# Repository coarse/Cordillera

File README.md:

# Cordillera

## About

The Cordillera PCB is an open design PCB heavily based on the Alice PCB. The only breaking change is the USB connector which renders it unusable on most Alice cases.

- STM32F072 controller
- USB C connector mounted at the top
- ESD, over voltage, and over current protection circuits
- Dual common cathode diodes instead of single ones
- Backlight, single color
- Fancy "press to reset, hold for bootloader" reset circuit

## Dependencies

Symbols and footprints used are from my [KiCad library](https://github.com/coarse/KiCad-Keeb-Lib)

## Notes

- Original Alice uses USB Mini, so this PCB may be incompatible with some Alice cases

## Disclaimer

I provide this design as a reference for designing similar keyboard layout PCBs. Using them within your projects will require a will to do research of one's own and to learn the workings of them, potentially fixing issues if they exist.

I present the design as-is and as-available, without liability and without any guarantees regarding functionality, as expressed in the license.

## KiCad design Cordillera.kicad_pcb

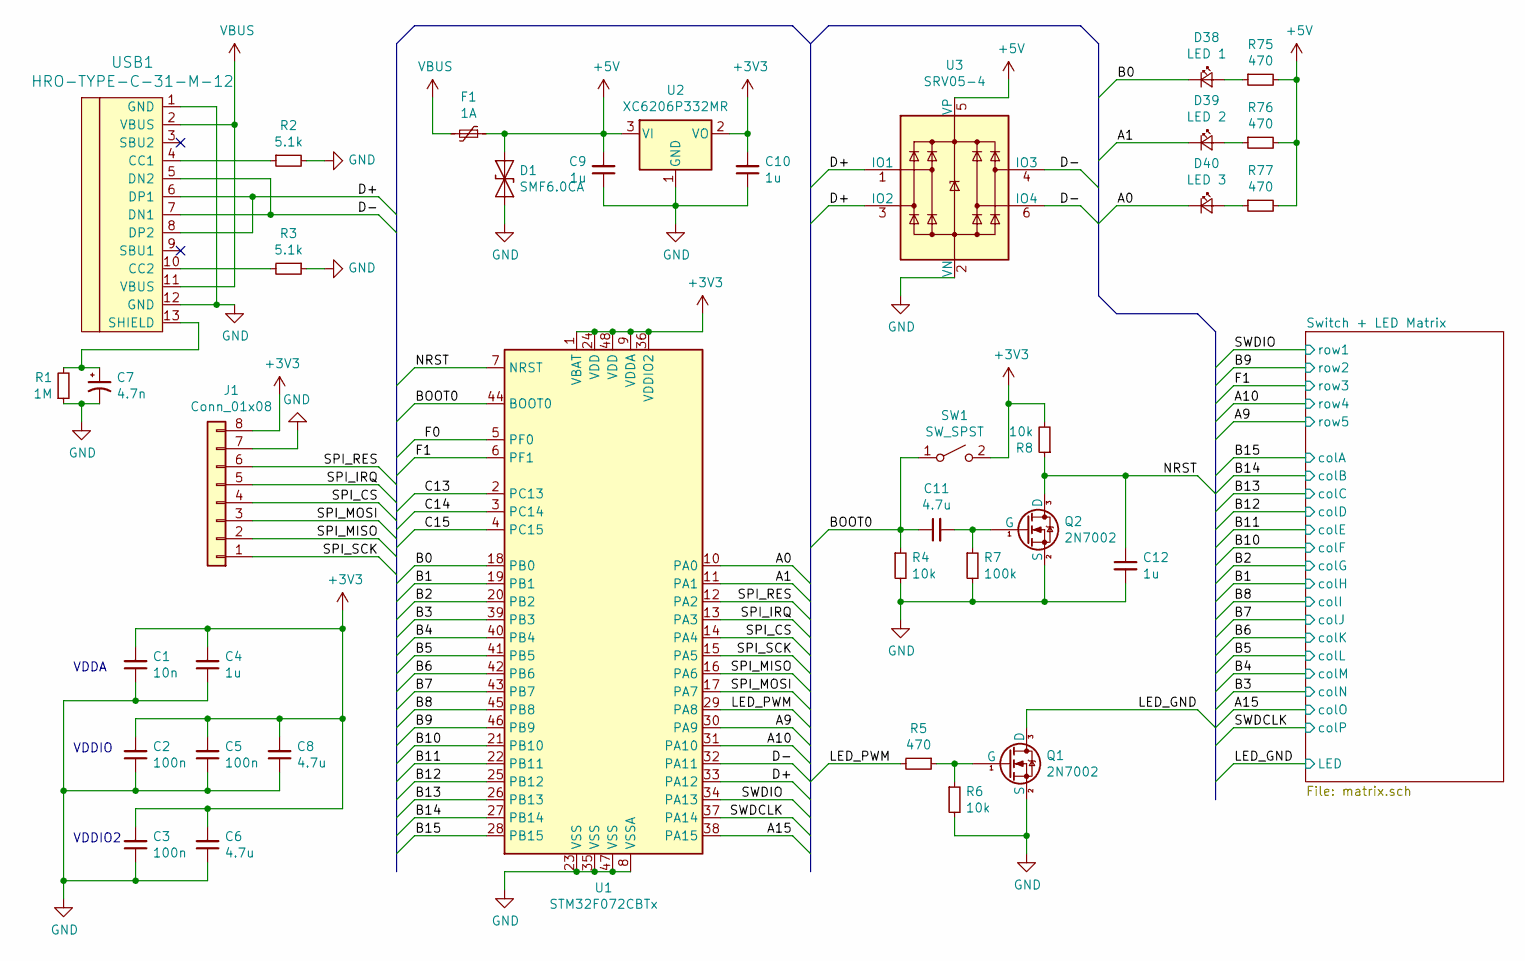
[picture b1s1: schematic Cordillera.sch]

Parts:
C1: 10n; C_0603_1608Metric
C2, C3, C5: 100n; C_0603_1608Metric
C4, C9, C10, C12: 1u; C_0603_1608Metric
C6, C8, C11: 4.7u; C_0603_1608Metric
C7: 4.7n; C_0603_1608Metric
D1: SMF6.0CA; D_SOD-123
D38: LED 1; LED_D3.0mm
D39: LED 2; LED_D3.0mm
D40: LED 3; LED_D3.0mm
F1: 1A; Fuse_1206_3216Metric
J1: Conn_01x08; PinHeader_2x04_P2.54mm_Vertical
Q1, Q2: 2N7002; SOT-23
R1: 1M; R_0603_1608Metric
R2, R3: 5.1k; R_0603_1608Metric
R4, R6, R8: 10k; R_0603_1608Metric
R5, R75, R76, R77: 470; R_0603_1608Metric
R7: 100k; R_0603_1608Metric
SW1: SW_SPST; TactSwitch_SPST_5.1x5.1mm
U1: STM32F072CBTx; LQFP-48_7x7mm_P0.5mm
U2: XC6206P332MR; SOT-23
U3: SRV05-4; SOT-23-6
USB1: HRO-TYPE-C-31-M-12

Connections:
+3V3: C1.2, C2.2, C3.2, C4.2, C5.2, C6.2, C8.2, C10.2, J1.8, R8.2, SW1.2 (B), U1.1 (VBAT), U1.9 (VDDA), U1.24 (VDD), U1.36 (VDDIO2), U1.48 (VDD), U2.2 (VO)
+5V: C9.2, D1.1 (A1), F1.1, R75.2, R76.2, R77.2, U2.3 (VI), U3.5 (VP); also elsewhere on the board
/A0: D40.1 (K), U1.10 (PA0)
/A1: D39.1 (K), U1.11 (PA1)
/A9: U1.30 (PA9); also elsewhere on the board
/A10: U1.31 (PA10); also elsewhere on the board
/A15: U1.38 (PA15); also elsewhere on the board
/B0: D38.1 (K), U1.18 (PB0)
/B1: U1.19 (PB1); also elsewhere on the board
/B2: U1.20 (PB2); also elsewhere on the board
/B3: U1.39 (PB3); also elsewhere on the board
/B4: U1.40 (PB4); also elsewhere on the board
/B5: U1.41 (PB5); also elsewhere on the board
/B6: U1.42 (PB6); also elsewhere on the board
/B7: U1.43 (PB7); also elsewhere on the board
/B8: U1.45 (PB8); also elsewhere on the board
/B9: U1.46 (PB9); also elsewhere on the board
/B10: U1.21 (PB10); also elsewhere on the board
/B11: U1.22 (PB11); also elsewhere on the board
/B12: U1.25 (PB12); also elsewhere on the board
/B13: U1.26 (PB13); also elsewhere on the board
/B14: U1.27 (PB14); also elsewhere on the board
/B15: U1.28 (PB15); also elsewhere on the board
/BOOT0: C11.1, R4.1, SW1.1 (A), U1.44 (BOOT0)
/C13: U1.2 (PC13)
/C14: U1.3 (PC14)
/C15: U1.4 (PC15)
/D+: U1.33 (PA12), U3.1 (IO1), U3.3 (IO2), USB1.6 (DP1), USB1.8 (DP2)
/D-: U1.32 (PA11), U3.4 (IO3), U3.6 (IO4), USB1.5 (DN2), USB1.7 (DN1)
/F0: U1.5 (PF0)
/F1: U1.6 (PF1); also elsewhere on the board
/LED_GND: Q1.3 (D); also elsewhere on the board
/LED_PWM: R5.2, U1.29 (PA8)
/NRST: C12.1, Q2.3 (D), R8.1, U1.7 (NRST)
/SPI_CS: J1.4, U1.14 (PA4)
/SPI_IRQ: J1.5, U1.13 (PA3)
/SPI_MISO: J1.2, U1.16 (PA6)
/SPI_MOSI: J1.3, U1.17 (PA7)
/SPI_RES: J1.6, U1.12 (PA2)
/SPI_SCK: J1.1, U1.15 (PA5)
/SWDCLK: U1.37 (PA14); also elsewhere on the board
/SWDIO: U1.34 (PA13); also elsewhere on the board
GND: C1.1, C2.1, C3.1, C4.1, C5.1, C6.1, C7.2, C8.1, C9.1, C10.1, C12.2, D1.2 (A2), J1.7, Q1.2 (S), Q2.2 (S), R1.1, R2.2, R3.1, R4.2, R6.2, R7.2, U1.8 (VSSA), U1.23 (VSS), U1.35 (VSS), U1.47 (VSS), U2.1 (GND), U3.2 (VN), USB1.1 (GND), USB1.12 (GND)
unnamed: C7.1, R1.2, USB1.13 (SHIELD)
unnamed: C11.2, Q2.1 (G), R7.1
unnamed: D38.2 (A), R75.1
unnamed: D39.2 (A), R76.1
unnamed: D40.2 (A), R77.1
unnamed: Q1.1 (G), R5.1, R6.1
unnamed: R2.1, USB1.4 (CC1)
unnamed: R3.2, USB1.10 (CC2)
VBUS: F1.2, USB1.2 (VBUS), USB1.11 (VBUS)

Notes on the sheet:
VDDIO
VDDIO2
VDDA

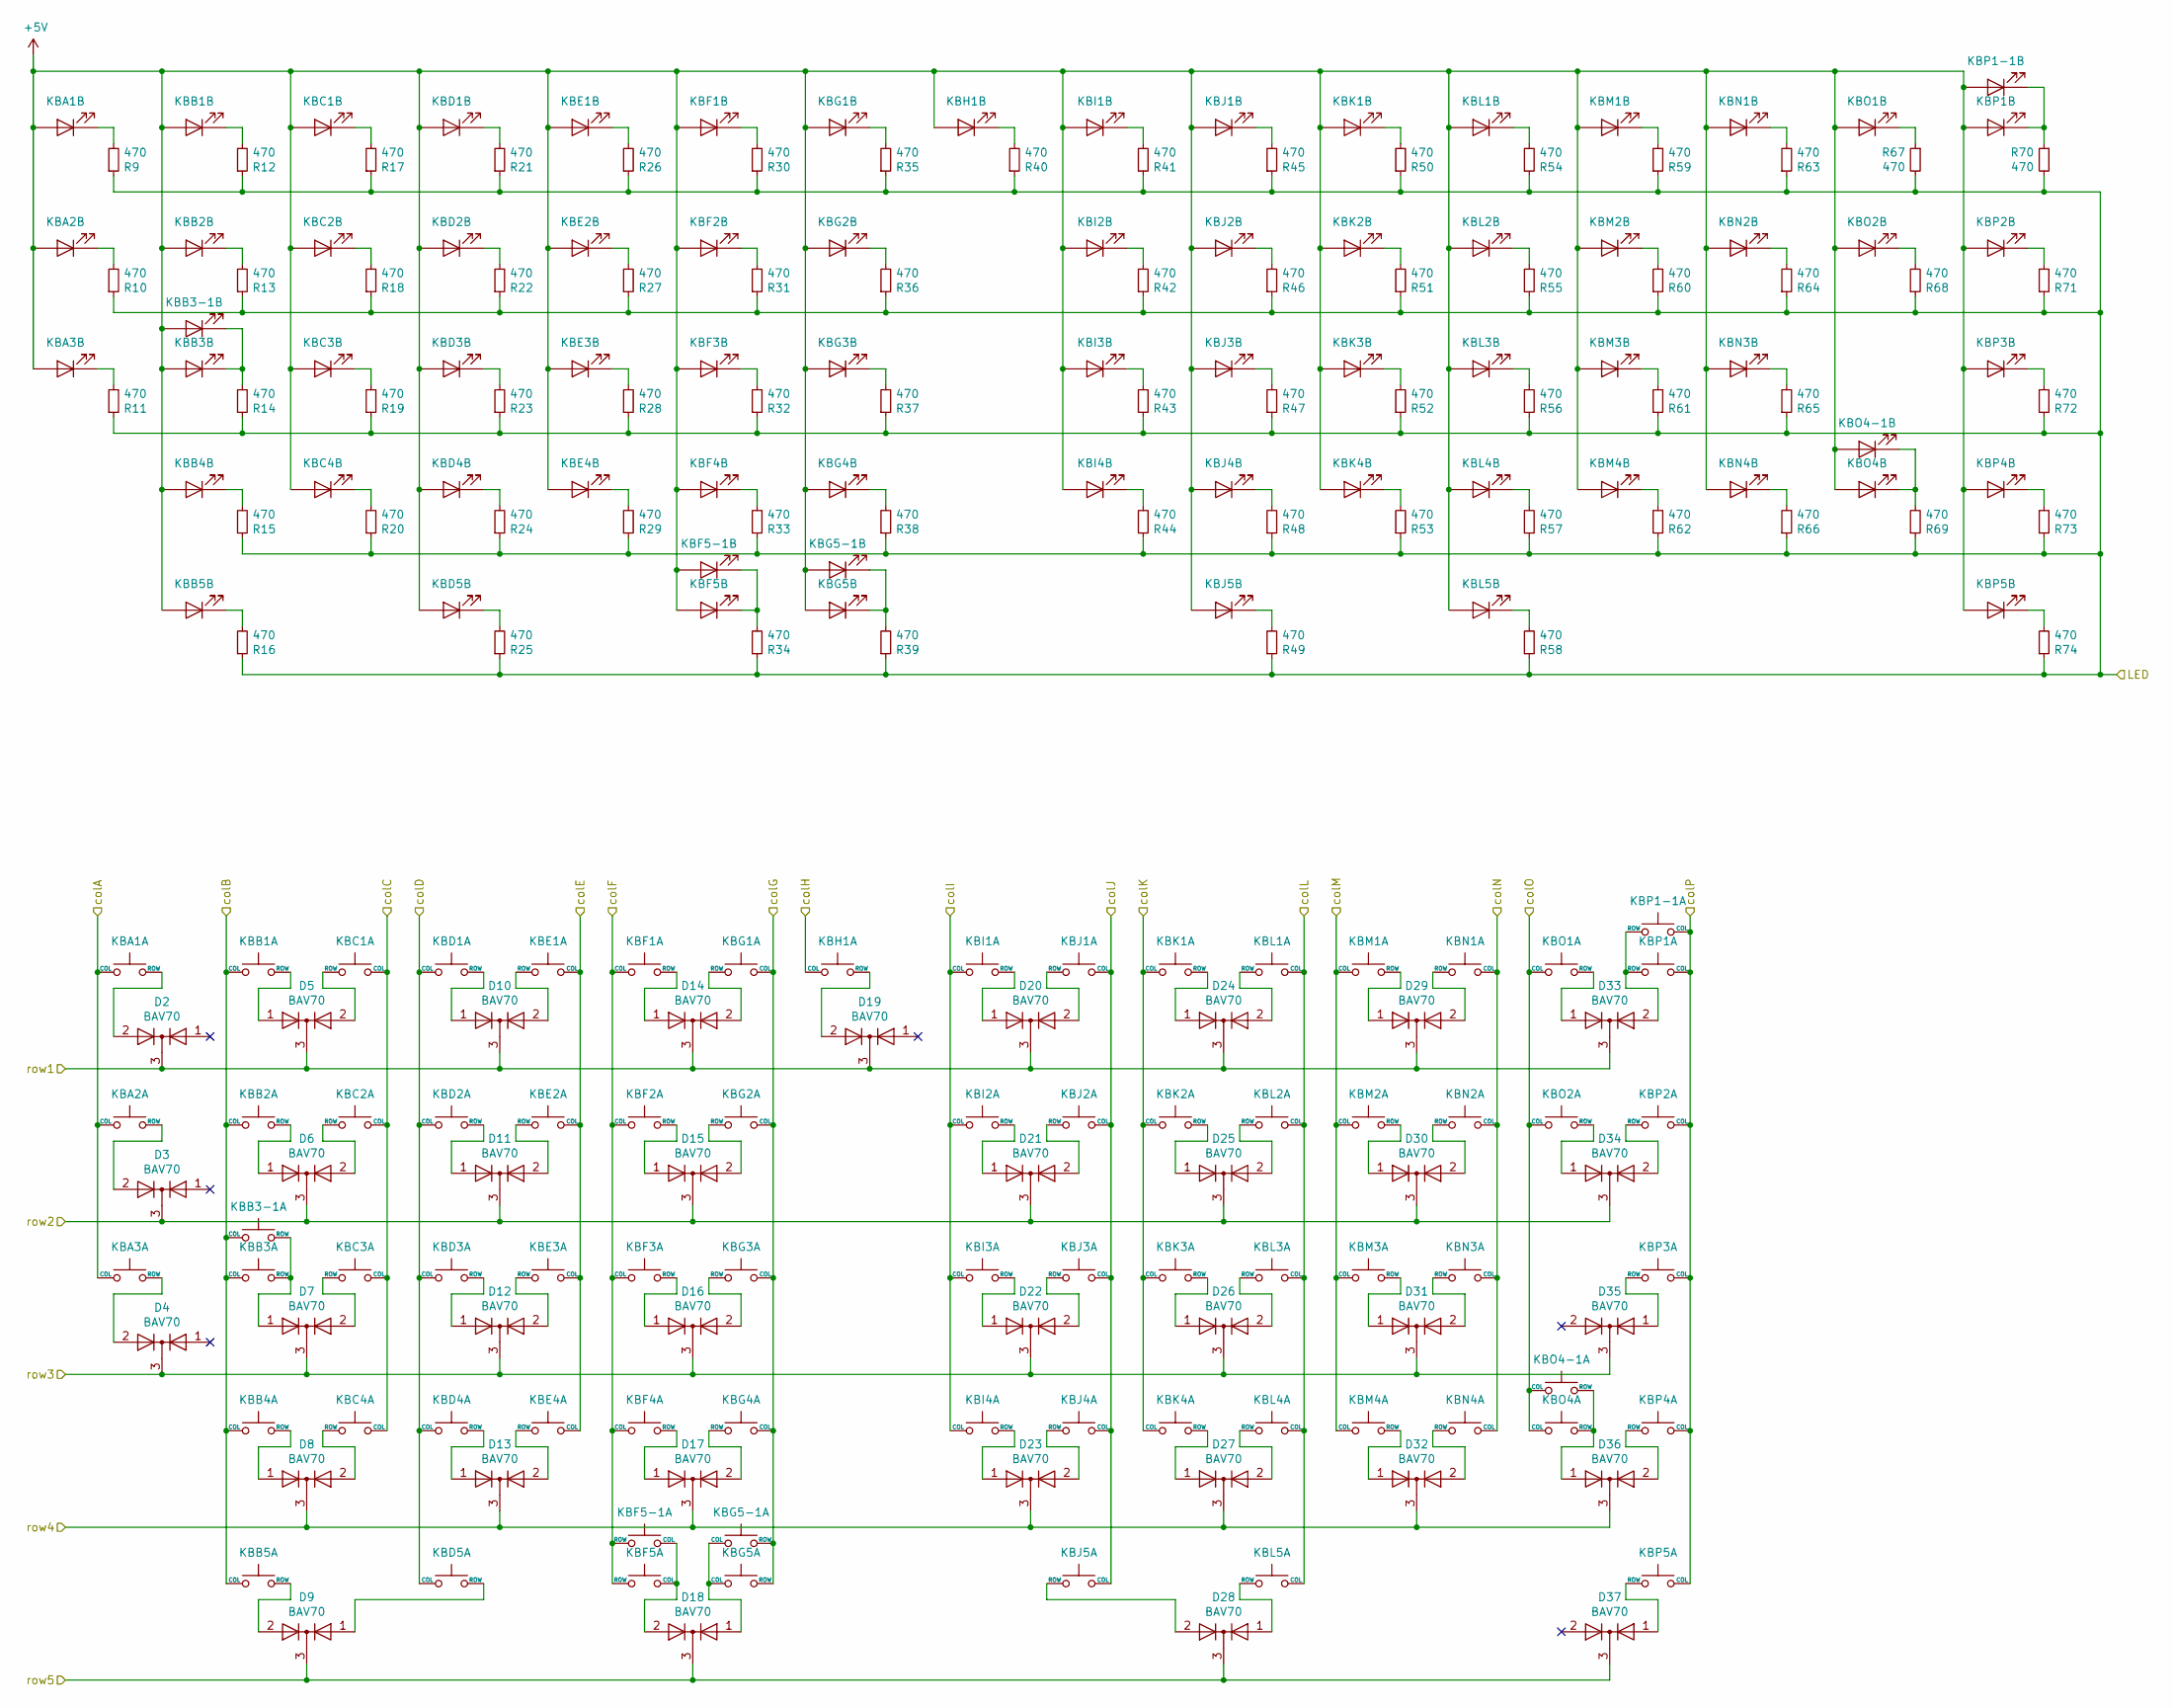
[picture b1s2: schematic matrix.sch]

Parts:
D2, D3, D4, D5, D6, D7, D8, D9, D10, D11, D12, D13, D14, D15, D16, D17, D18, D19, D20, D21, D22, D23, D24, D25, D26, D27, D28, D29, D30, D31, D32, D33, D34, D35, D36, D37: BAV70; SOT-23
KBA1, KBA2, KBA3: Keyboard_Switch; MXOnly-1U
KBB1: Keyboard_Switch; MXOnly-1U
KBB2, KBB5: Keyboard_Switch; MXOnly-1.5U
KBB3: Keyboard_Switch; MXOnly-1.75U
KBB3-1: Keyboard_Switch; MXOnly-1.25U-FLIPPED
KBB4: Keyboard_Switch; MXOnly-2.25U
KBC1, KBC2, KBC3, KBC4: Keyboard_Switch; MXOnly-1U
KBD1, KBD2, KBD3, KBD4: Keyboard_Switch; MXOnly-1U
KBD5: Keyboard_Switch; MXOnly-1.5U
KBE1, KBE2, KBE3, KBE4: Keyboard_Switch; MXOnly-1U
KBF1, KBF2, KBF3, KBF4: Keyboard_Switch; MXOnly-1U
KBF5: Keyboard_Switch; MXOnly-2U-FLIPPED-ReversedStabilizers
KBF5-1: Keyboard_Switch; MXOnly-2.25U-ReversedStabilizers
KBG1, KBG2, KBG3, KBG4, KBG5-1: Keyboard_Switch; MXOnly-1U
KBG5: Keyboard_Switch; MXOnly-1.25U-FLIPPED
KBH1: Keyboard_Switch; MXOnly-1U
KBI1, KBI2, KBI3, KBI4: Keyboard_Switch; MXOnly-1U
KBJ1, KBJ2, KBJ3, KBJ4: Keyboard_Switch; MXOnly-1U
KBJ5: Keyboard_Switch; MXOnly-2.75U-ReversedStabilizers
KBK1, KBK2, KBK3, KBK4: Keyboard_Switch; MXOnly-1U
KBL1, KBL2, KBL3, KBL4: Keyboard_Switch; MXOnly-1U
KBL5: Keyboard_Switch; MXOnly-1.5U
KBM1, KBM2, KBM3, KBM4: Keyboard_Switch; MXOnly-1U
KBN1, KBN2, KBN3, KBN4: Keyboard_Switch; MXOnly-1U
KBO1, KBO2: Keyboard_Switch; MXOnly-1U
KBO4: Keyboard_Switch; MXOnly-2.75U
KBO4-1: Keyboard_Switch; MXOnly-1.75U-FLIPPED
KBP1: Keyboard_Switch; MXOnly-2U
KBP1-1: Keyboard_Switch; MXOnly-1U-FLIPPED
KBP2, KBP5: Keyboard_Switch; MXOnly-1.5U
KBP3: Keyboard_Switch; MXOnly-2.25U-ReversedStabilizers
KBP4: Keyboard_Switch; MXOnly-1U
R9, R10, R11, R12, R13, R14, R15, R16, R17, R18, R19, R20, R21, R22, R23, R24, R25, R26, R27, R28, R29, R30, R31, R32, R33, R34, R35, R36, R37, R38, R39, R40, R41, R42, R43, R44, R45, R46, R47, R48, R49, R50, R51, R52, R53, R54, R55, R56, R57, R58, R59, R60, R61, R62, R63, R64, R65, R66, R67, R68, R69, R70, R71, R72, R73, R74: 470; R_0603_1608Metric

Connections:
+5V: KBA1.3 (LED), KBA2.3 (LED), KBA3.3 (LED), KBB1.3 (LED), KBB2.3 (LED), KBB3.3 (LED), KBB3-1.3 (LED), KBB4.3 (LED), KBB5.3 (LED), KBC1.3 (LED), KBC2.3 (LED), KBC3.3 (LED), KBC4.3 (LED), KBD1.3 (LED), KBD2.3 (LED), KBD3.3 (LED), KBD4.3 (LED), KBD5.3 (LED), KBE1.3 (LED), KBE2.3 (LED), KBE3.3 (LED), KBE4.3 (LED), KBF1.3 (LED), KBF2.3 (LED), KBF3.3 (LED), KBF4.3 (LED), KBF5.3 (LED), KBF5-1.3 (LED), KBG1.3 (LED), KBG2.3 (LED), KBG3.3 (LED), KBG4.3 (LED), KBG5.3 (LED), KBG5-1.3 (LED), KBH1.3 (LED), KBI1.3 (LED), KBI2.3 (LED), KBI3.3 (LED), KBI4.3 (LED), KBJ1.3 (LED), KBJ2.3 (LED), KBJ3.3 (LED), KBJ4.3 (LED), KBJ5.3 (LED), KBK1.3 (LED), KBK2.3 (LED), KBK3.3 (LED), KBK4.3 (LED), KBL1.3 (LED), KBL2.3 (LED), KBL3.3 (LED), KBL4.3 (LED), KBL5.3 (LED), KBM1.3 (LED), KBM2.3 (LED), KBM3.3 (LED), KBM4.3 (LED), KBN1.3 (LED), KBN2.3 (LED), KBN3.3 (LED), KBN4.3 (LED), KBO1.3 (LED), KBO2.3 (LED), KBO4.3 (LED), KBO4-1.3 (LED), KBP1.3 (LED), KBP1-1.3 (LED), KBP2.3 (LED), KBP3.3 (LED), KBP4.3 (LED), KBP5.3 (LED); also elsewhere on the board
/A9: D9.3 (K), D18.3 (K), D28.3 (K), D37.3 (K); also elsewhere on the board
/A10: D8.3 (K), D13.3 (K), D17.3 (K), D23.3 (K), D27.3 (K), D32.3 (K), D36.3 (K); also elsewhere on the board
/A15: KBO1.1 (COL), KBO2.1 (COL), KBO4.1 (COL), KBO4-1.1 (COL); also elsewhere on the board
/B1: KBH1.1 (COL); also elsewhere on the board
/B2: KBG1.1 (COL), KBG2.1 (COL), KBG3.1 (COL), KBG4.1 (COL), KBG5.2 (ROW), KBG5-1.2 (ROW); also elsewhere on the board
/B3: KBN1.1 (COL), KBN2.1 (COL), KBN3.1 (COL), KBN4.1 (COL); also elsewhere on the board
/B4: KBM1.1 (COL), KBM2.1 (COL), KBM3.1 (COL), KBM4.1 (COL); also elsewhere on the board
/B5: KBL1.1 (COL), KBL2.1 (COL), KBL3.1 (COL), KBL4.1 (COL), KBL5.1 (COL); also elsewhere on the board
/B6: KBK1.1 (COL), KBK2.1 (COL), KBK3.1 (COL), KBK4.1 (COL); also elsewhere on the board
/B7: KBJ1.1 (COL), KBJ2.1 (COL), KBJ3.1 (COL), KBJ4.1 (COL), KBJ5.1 (COL); also elsewhere on the board
/B8: KBI1.1 (COL), KBI2.1 (COL), KBI3.1 (COL), KBI4.1 (COL); also elsewhere on the board
/B9: D3.3 (K), D6.3 (K), D11.3 (K), D15.3 (K), D21.3 (K), D25.3 (K), D30.3 (K), D34.3 (K); also elsewhere on the board
/B10: KBF1.1 (COL), KBF2.1 (COL), KBF3.1 (COL), KBF4.1 (COL), KBF5.2 (ROW), KBF5-1.2 (ROW); also elsewhere on the board
/B11: KBE1.1 (COL), KBE2.1 (COL), KBE3.1 (COL), KBE4.1 (COL); also elsewhere on the board
/B12: KBD1.1 (COL), KBD2.1 (COL), KBD3.1 (COL), KBD4.1 (COL), KBD5.1 (COL); also elsewhere on the board
/B13: KBC1.1 (COL), KBC2.1 (COL), KBC3.1 (COL), KBC4.1 (COL); also elsewhere on the board
/B14: KBB1.1 (COL), KBB2.1 (COL), KBB3.1 (COL), KBB3-1.1 (COL), KBB4.1 (COL), KBB5.1 (COL); also elsewhere on the board
/B15: KBA1.1 (COL), KBA2.1 (COL), KBA3.1 (COL); also elsewhere on the board
/F1: D4.3 (K), D7.3 (K), D12.3 (K), D16.3 (K), D22.3 (K), D26.3 (K), D31.3 (K), D35.3 (K); also elsewhere on the board
/LED_GND: R9.1, R10.1, R11.1, R12.1, R13.1, R14.1, R15.1, R16.1, R17.1, R18.1, R19.1, R20.1, R21.1, R22.1, R23.1, R24.1, R25.1, R26.1, R27.1, R28.1, R29.1, R30.1, R31.1, R32.1, R33.1, R34.1, R35.1, R36.1, R37.1, R38.1, R39.1, R40.1, R41.1, R42.1, R43.1, R44.1, R45.1, R46.1, R47.1, R48.1, R49.1, R50.1, R51.1, R52.1, R53.1, R54.1, R55.1, R56.1, R57.1, R58.1, R59.1, R60.1, R61.1, R62.1, R63.1, R64.1, R65.1, R66.1, R67.2, R68.1, R69.1, R70.2, R71.1, R72.1, R73.1, R74.1; also elsewhere on the board
/SWDCLK: KBP1.1 (COL), KBP1-1.1 (COL), KBP2.1 (COL), KBP3.1 (COL), KBP4.1 (COL), KBP5.1 (COL); also elsewhere on the board
/SWDIO: D2.3 (K), D5.3 (K), D10.3 (K), D14.3 (K), D19.3 (K), D20.3 (K), D24.3 (K), D29.3 (K), D33.3 (K); also elsewhere on the board
unnamed: D2.2 (A), KBA1.2 (ROW)
unnamed: D3.2 (A), KBA2.2 (ROW)
unnamed: D4.2 (A), KBA3.2 (ROW)
unnamed: D5.1 (A), KBB1.2 (ROW)
unnamed: D5.2 (A), KBC1.2 (ROW)
unnamed: D6.1 (A), KBB2.2 (ROW)
unnamed: D6.2 (A), KBC2.2 (ROW)
unnamed: D7.1 (A), KBB3.2 (ROW), KBB3-1.2 (ROW)
unnamed: D7.2 (A), KBC3.2 (ROW)
unnamed: D8.1 (A), KBB4.2 (ROW)
unnamed: D8.2 (A), KBC4.2 (ROW)
unnamed: D9.1 (A), KBD5.2 (ROW)
unnamed: D9.2 (A), KBB5.2 (ROW)
unnamed: D10.1 (A), KBD1.2 (ROW)
unnamed: D10.2 (A), KBE1.2 (ROW)
unnamed: D11.1 (A), KBD2.2 (ROW)
unnamed: D11.2 (A), KBE2.2 (ROW)
unnamed: D12.1 (A), KBD3.2 (ROW)
unnamed: D12.2 (A), KBE3.2 (ROW)
unnamed: D13.1 (A), KBD4.2 (ROW)
unnamed: D13.2 (A), KBE4.2 (ROW)
unnamed: D14.1 (A), KBF1.2 (ROW)
unnamed: D14.2 (A), KBG1.2 (ROW)
unnamed: D15.1 (A), KBF2.2 (ROW)
unnamed: D15.2 (A), KBG2.2 (ROW)
unnamed: D16.1 (A), KBF3.2 (ROW)
unnamed: D16.2 (A), KBG3.2 (ROW)
unnamed: D17.1 (A), KBF4.2 (ROW)
unnamed: D17.2 (A), KBG4.2 (ROW)
unnamed: D18.1 (A), KBG5.1 (COL), KBG5-1.1 (COL)
unnamed: D18.2 (A), KBF5.1 (COL), KBF5-1.1 (COL)
unnamed: D19.2 (A), KBH1.2 (ROW)
unnamed: D20.1 (A), KBI1.2 (ROW)
unnamed: D20.2 (A), KBJ1.2 (ROW)
unnamed: D21.1 (A), KBI2.2 (ROW)
unnamed: D21.2 (A), KBJ2.2 (ROW)
unnamed: D22.1 (A), KBI3.2 (ROW)
unnamed: D22.2 (A), KBJ3.2 (ROW)
unnamed: D23.1 (A), KBI4.2 (ROW)
unnamed: D23.2 (A), KBJ4.2 (ROW)
unnamed: D24.1 (A), KBK1.2 (ROW)
unnamed: D24.2 (A), KBL1.2 (ROW)
unnamed: D25.1 (A), KBK2.2 (ROW)
unnamed: D25.2 (A), KBL2.2 (ROW)
unnamed: D26.1 (A), KBK3.2 (ROW)
unnamed: D26.2 (A), KBL3.2 (ROW)
unnamed: D27.1 (A), KBK4.2 (ROW)
unnamed: D27.2 (A), KBL4.2 (ROW)
unnamed: D28.1 (A), KBL5.2 (ROW)
unnamed: D28.2 (A), KBJ5.2 (ROW)
unnamed: D29.1 (A), KBM1.2 (ROW)
unnamed: D29.2 (A), KBN1.2 (ROW)
unnamed: D30.1 (A), KBM2.2 (ROW)
unnamed: D30.2 (A), KBN2.2 (ROW)
unnamed: D31.1 (A), KBM3.2 (ROW)
unnamed: D31.2 (A), KBN3.2 (ROW)
unnamed: D32.1 (A), KBM4.2 (ROW)
unnamed: D32.2 (A), KBN4.2 (ROW)
unnamed: D33.1 (A), KBO1.2 (ROW)
unnamed: D33.2 (A), KBP1.2 (ROW), KBP1-1.2 (ROW)
unnamed: D34.1 (A), KBO2.2 (ROW)
unnamed: D34.2 (A), KBP2.2 (ROW)
unnamed: D35.1 (A), KBP3.2 (ROW)
unnamed: D36.1 (A), KBO4.2 (ROW), KBO4-1.2 (ROW)
unnamed: D36.2 (A), KBP4.2 (ROW)
unnamed: D37.1 (A), KBP5.2 (ROW)
unnamed: KBA1.4 (LEDGND), R9.2
unnamed: KBA2.4 (LEDGND), R10.2
unnamed: KBA3.4 (LEDGND), R11.2
unnamed: KBB1.4 (LEDGND), R12.2
unnamed: KBB2.4 (LEDGND), R13.2
unnamed: KBB3.4 (LEDGND), KBB3-1.4 (LEDGND), R14.2
unnamed: KBB4.4 (LEDGND), R15.2
unnamed: KBB5.4 (LEDGND), R16.2
unnamed: KBC1.4 (LEDGND), R17.2
unnamed: KBC2.4 (LEDGND), R18.2
unnamed: KBC3.4 (LEDGND), R19.2
unnamed: KBC4.4 (LEDGND), R20.2
unnamed: KBD1.4 (LEDGND), R21.2
unnamed: KBD2.4 (LEDGND), R22.2
unnamed: KBD3.4 (LEDGND), R23.2
unnamed: KBD4.4 (LEDGND), R24.2
unnamed: KBD5.4 (LEDGND), R25.2
unnamed: KBE1.4 (LEDGND), R26.2
unnamed: KBE2.4 (LEDGND), R27.2
unnamed: KBE3.4 (LEDGND), R28.2
unnamed: KBE4.4 (LEDGND), R29.2
unnamed: KBF1.4 (LEDGND), R30.2
unnamed: KBF2.4 (LEDGND), R31.2
unnamed: KBF3.4 (LEDGND), R32.2
unnamed: KBF4.4 (LEDGND), R33.2
unnamed: KBF5.4 (LEDGND), KBF5-1.4 (LEDGND), R34.2
unnamed: KBG1.4 (LEDGND), R35.2
unnamed: KBG2.4 (LEDGND), R36.2
unnamed: KBG3.4 (LEDGND), R37.2
unnamed: KBG4.4 (LEDGND), R38.2
unnamed: KBG5.4 (LEDGND), KBG5-1.4 (LEDGND), R39.2
unnamed: KBH1.4 (LEDGND), R40.2
unnamed: KBI1.4 (LEDGND), R41.2
unnamed: KBI2.4 (LEDGND), R42.2
unnamed: KBI3.4 (LEDGND), R43.2
unnamed: KBI4.4 (LEDGND), R44.2
unnamed: KBJ1.4 (LEDGND), R45.2
unnamed: KBJ2.4 (LEDGND), R46.2
unnamed: KBJ3.4 (LEDGND), R47.2
unnamed: KBJ4.4 (LEDGND), R48.2
unnamed: KBJ5.4 (LEDGND), R49.2
unnamed: KBK1.4 (LEDGND), R50.2
unnamed: KBK2.4 (LEDGND), R51.2
unnamed: KBK3.4 (LEDGND), R52.2
unnamed: KBK4.4 (LEDGND), R53.2
unnamed: KBL1.4 (LEDGND), R54.2
unnamed: KBL2.4 (LEDGND), R55.2
unnamed: KBL3.4 (LEDGND), R56.2
unnamed: KBL4.4 (LEDGND), R57.2
unnamed: KBL5.4 (LEDGND), R58.2
unnamed: KBM1.4 (LEDGND), R59.2
unnamed: KBM2.4 (LEDGND), R60.2
unnamed: KBM3.4 (LEDGND), R61.2
unnamed: KBM4.4 (LEDGND), R62.2
unnamed: KBN1.4 (LEDGND), R63.2
unnamed: KBN2.4 (LEDGND), R64.2
unnamed: KBN3.4 (LEDGND), R65.2
unnamed: KBN4.4 (LEDGND), R66.2
unnamed: KBO1.4 (LEDGND), R67.1
unnamed: KBO2.4 (LEDGND), R68.2
unnamed: KBO4.4 (LEDGND), KBO4-1.4 (LEDGND), R69.2
unnamed: KBP1.4 (LEDGND), KBP1-1.4 (LEDGND), R70.1
unnamed: KBP2.4 (LEDGND), R71.2
unnamed: KBP3.4 (LEDGND), R72.2
unnamed: KBP4.4 (LEDGND), R73.2
unnamed: KBP5.4 (LEDGND), R74.2

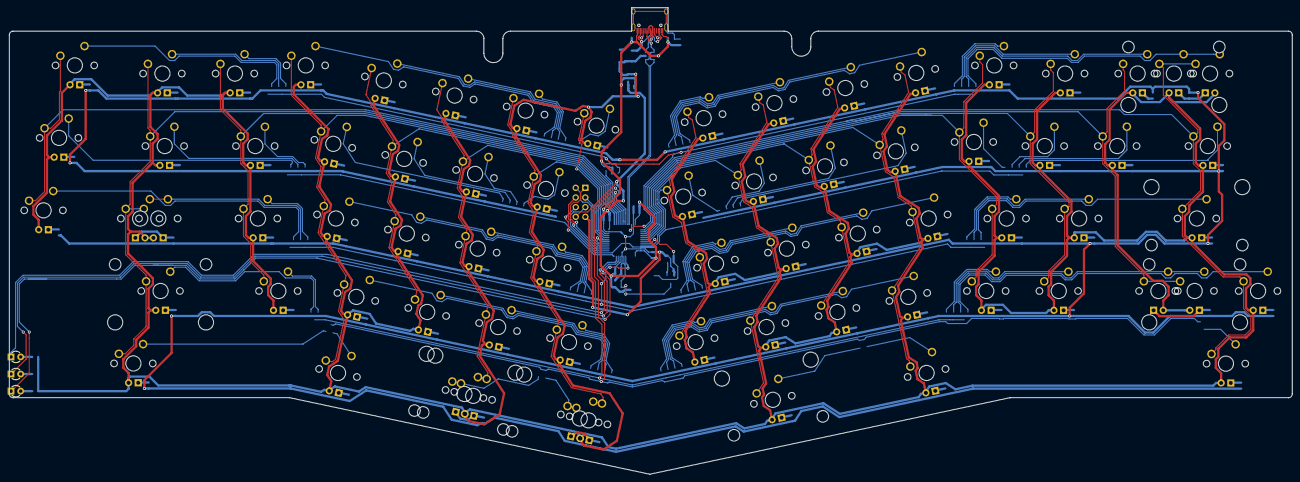
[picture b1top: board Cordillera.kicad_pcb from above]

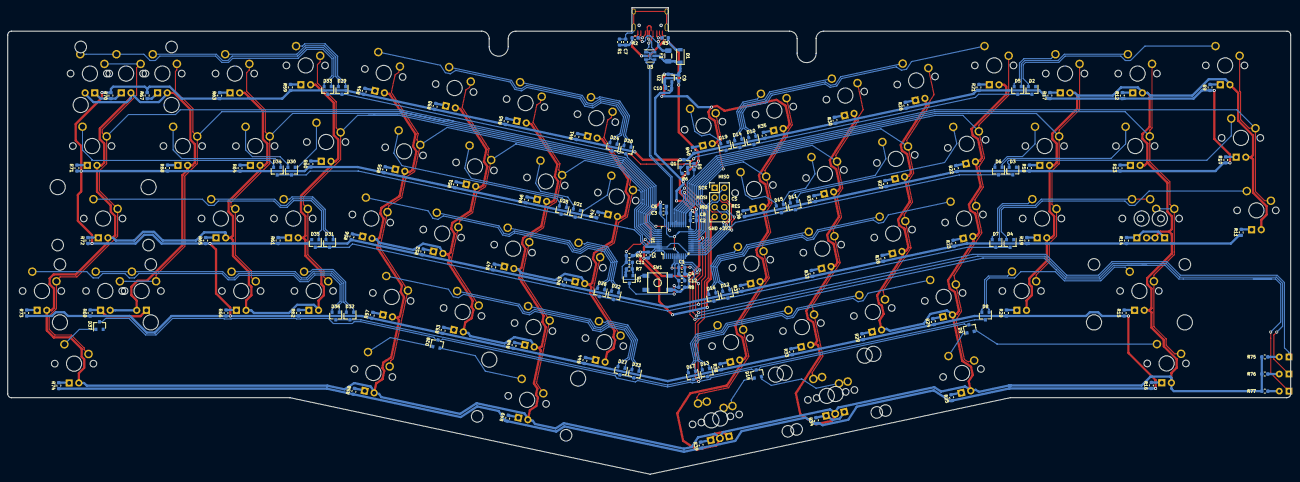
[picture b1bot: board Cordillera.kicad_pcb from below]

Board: 2 copper layers, 337.2 x 122.6 mm, 209 parts (134 on the bottom side), 180 nets.

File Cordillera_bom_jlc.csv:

Comment,Designator,Footprint,LCSC Part #,Manufacturer,Manufacturer Part Number
10n,C1,keeb_parts:C_0603_1608Metric,C1589,Samsung Electro-Mechanics,CL10B103KB8NNNC
100n,"C2,C3,C5",keeb_parts:C_0603_1608Metric,C1591,Samsung Electro-Mechanics,CL10B104KB8NNNC
4.7n,C7,keeb_parts:C_0603_1608Metric,C1621,Samsung Electro-Mechanics,CL10B472KB8NNNC
4.7u,"C6,C8,C11",keeb_parts:C_0603_1608Metric,C1705,Samsung Electro-Mechanics,CL10A475KP8NNNC
1u,"C4,C9,C10,C12",keeb_parts:C_0603_1608Metric,C1592,Samsung Electro-Mechanics,CL10A105KO8NNNC
SMF6.0CA,D1,keeb_parts:D_SOD-123,C123791,MDD(Microdiode Electronics),SMF6.0CA
BAV70,"D2,D3,D4,D5,D6,D7,D8,D9,D10,D11,D12,D13,D14,D15,D16,D17,D18,D19,D20,D21,D22,D23,D24,D25,D26,D27,D28,D29,D30,D31,D32,D33,D34,D35,D36,D37",keeb_parts:SOT-23,C2501,Nexperia,"BAV70,215"
1A,F1,keeb_parts:Fuse_1206_3216Metric,C151162,Littelfuse,1206L050/15YR
2N7002,"Q1,Q2",keeb_parts:SOT-23,C65189,Nexperia,"2N7002,215"
1M,R1,keeb_parts:R_0603_1608Metric,C26098,UNI-ROYAL(Uniroyal Elec),0603WAJ0105T5E
5.1k,"R2,R3",keeb_parts:R_0603_1608Metric,C26000,UNI-ROYAL(Uniroyal Elec),0603WAJ0512T5E
10k,"R4,R6,R8",keeb_parts:R_0603_1608Metric,C15401,UNI-ROYAL(Uniroyal Elec),0603WAJ0103T5E
470,"R5,R9,R10,R11,R12,R13,R14,R15,R16,R17,R18,R19,R20,R21,R22,R23,R24,R25,R26,R27,R28,R29,R30,R31,R32,R33,R34,R35,R36,R37,R38,R39,R40,R41,R42,R43,R44,R45,R46,R47,R48,R49,R50,R51,R52,R53,R54,R55,R56,R57,R58,R59,R60,R61,R62,R63,R64,R65,R66,R67,R68,R69,R70,R71,R72,R73,R74,R75,R76,R77",keeb_parts:R_0603_1608Metric,C1211,UNI-ROYAL(Uniroyal Elec),0603WAJ0470T5E
100k,R7,keeb_parts:R_0603_1608Metric,C15458,UNI-ROYAL(Uniroyal Elec),0603WAJ0104T5E
SW_SPST,SW1,keeb_parts:TactSwitch_SPST_5.1x5.1mm,C318884,XKB Connectivity,TS-1187A-B-A-B
STM32F072CBTx,U1,keeb_mcu:LQFP-48_7x7mm_P0.5mm,C81720,STMicroelectronics,STM32F072CBT6
XC6206P332MR,U2,keeb_parts:SOT-23,C5446,Torex Semicon,XC6206P332MR
SRV05-4,U3,keeb_parts:SOT-23-6,C85364,ProTek Devices,SRV05-4-P-T7
HRO-TYPE-C-31-M-12,USB1,keeb_connectors:HRO-TYPE-C-31-M-12,C165948,Korean Hroparts Elec,TYPE-C-31-M-12

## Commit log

2020-08-09 Remove plate drawing
2020-08-09 Add indicator LEDs
2020-08-09 Lay out switch and LED matrix components
2020-08-09 Finish routing LED matrix
2020-08-10 Do some routing
2020-08-11 Finish routing switches
2020-08-11 Finish column routing
2020-08-25 Update files
2020-08-25 Add renders
2020-08-25 fix indicator leds

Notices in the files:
README.md:
CC BY-NC-SA 4.0
